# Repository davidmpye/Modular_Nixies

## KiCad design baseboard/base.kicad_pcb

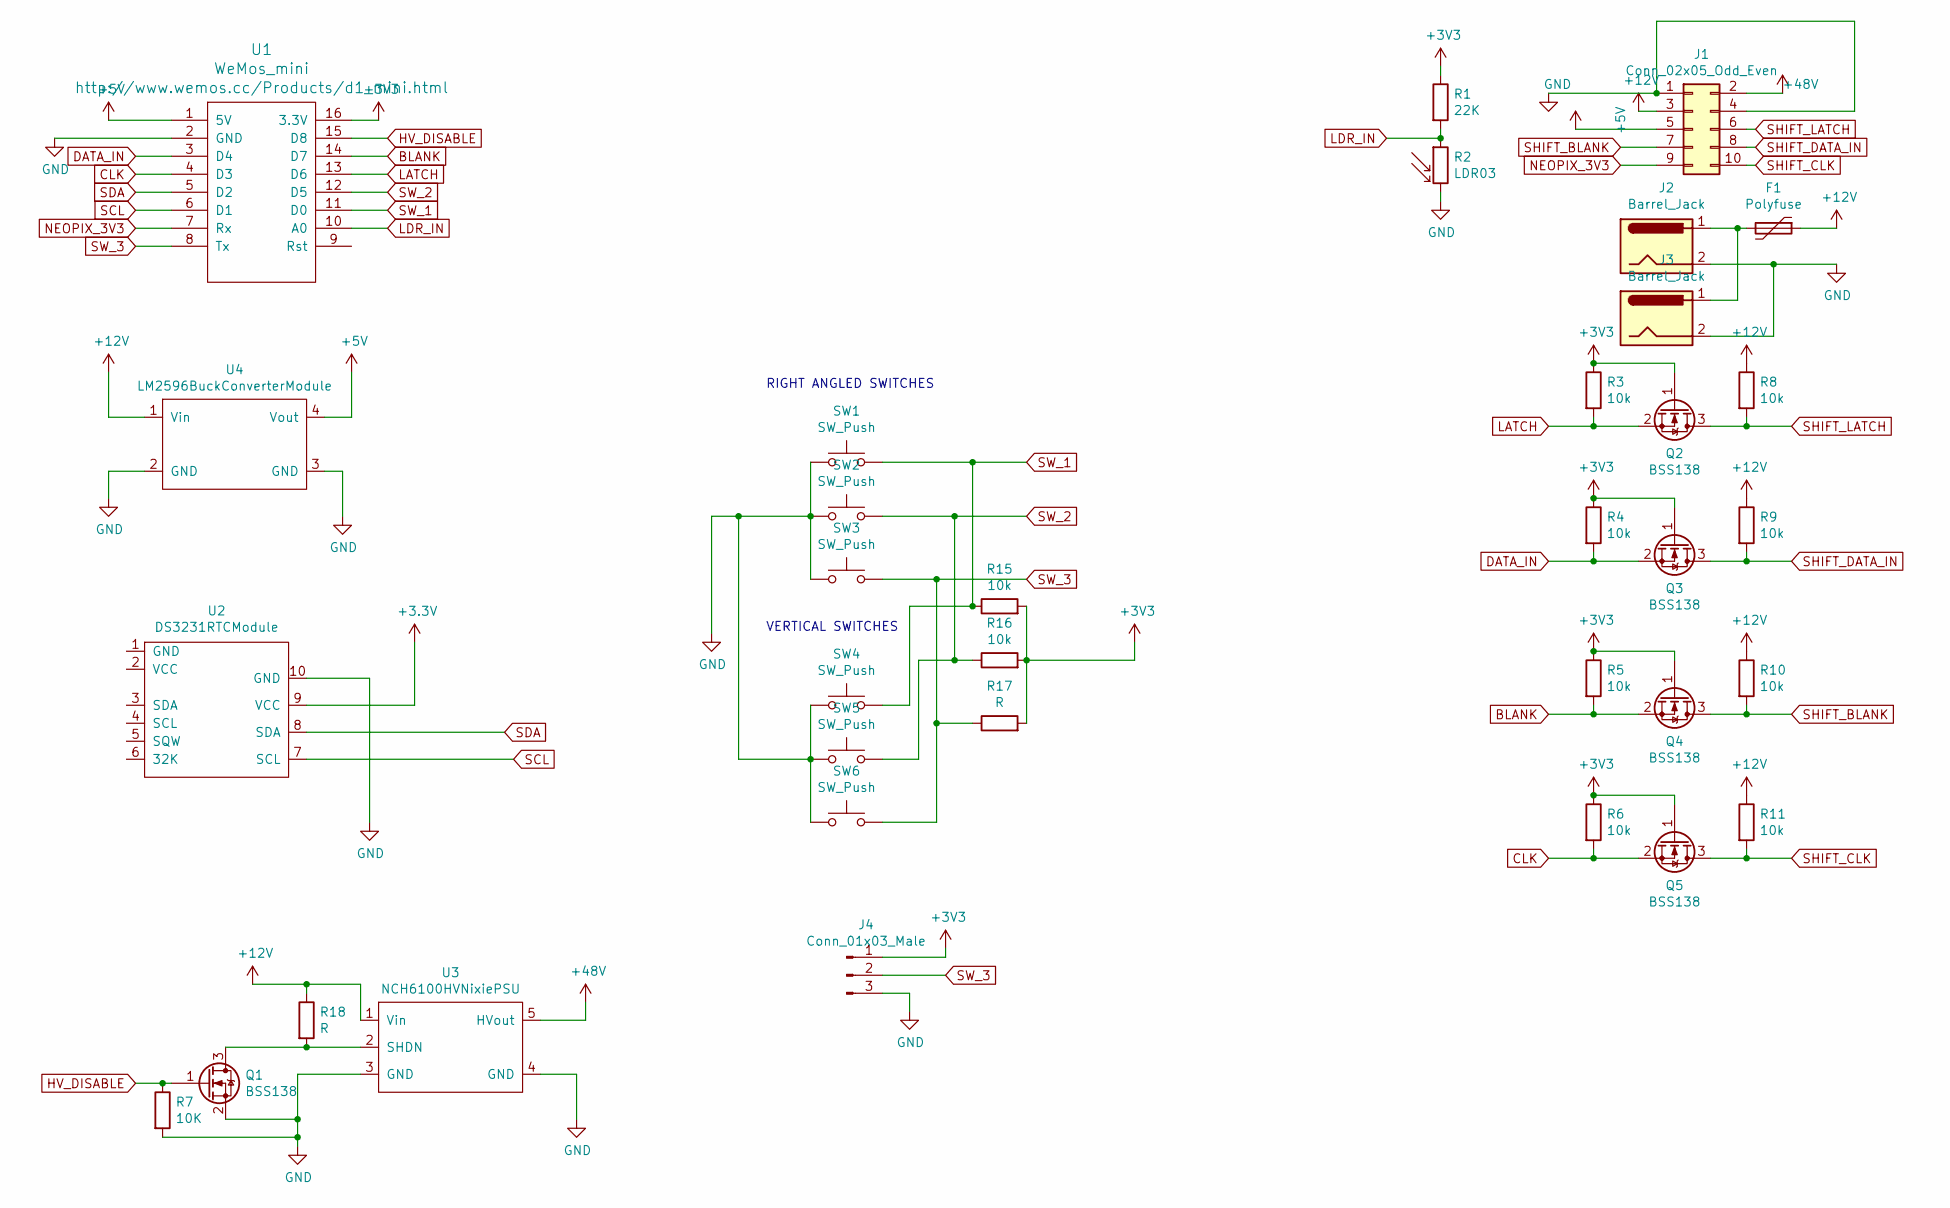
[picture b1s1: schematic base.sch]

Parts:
F1: Polyfuse; R_Axial_DIN0309_L9.0mm_D3.2mm_P15.24mm_Horizontal
J1: Conn_02x05_Odd_Even; PinHeader_2x05_P2.54mm_Vertical
J2: Barrel_Jack; BarrelJack_Horizontal
J3: Barrel_Jack; VerticalBarrel2.1mm
J4: Conn_01x03_Male; PinHeader_1x03_P2.54mm_Vertical
Q1, Q2, Q3, Q4, Q5: BSS138; SOT-23
R1: 22K; R_Axial_DIN0309_L9.0mm_D3.2mm_P12.70mm_Horizontal
R2: LDR03; R_Axial_DIN0204_L3.6mm_D1.6mm_P5.08mm_Vertical
R3, R4, R5, R6, R8, R9, R10, R11: 10k; R_0805_2012Metric_Pad1.15x1.40mm_HandSolder
R7: 10K; R_0805_2012Metric_Pad1.15x1.40mm_HandSolder
R15, R16: 10k; R_Axial_DIN0309_L9.0mm_D3.2mm_P12.70mm_Horizontal
R17, R18: R; R_Axial_DIN0309_L9.0mm_D3.2mm_P12.70mm_Horizontal
SW1, SW2, SW3: SW_Push; SW_Tactile_SKHH_Angled
SW4, SW5, SW6: SW_Push; SW_PUSH_6mm
U1: WeMos_mini; D1_mini_board
U2: DS3231RTCModule; DS3121RTCModule
U3: NCH6100HVNixiePSU
U4: LM2596BuckConverterModule

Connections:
+5V: J1.5, U1.1 (5V), U4.4 (Vout)
+12V: F1.1, J1.3, R8.1, R9.1, R10.1, R11.1, R18.1, U3.1 (Vin), U4.1 (Vin)
+48V: J1.2, U3.5 (HVout)
BLANK: Q4.2 (S), R5.2, U1.14 (D7)
CLK: Q5.2 (S), R6.2, U1.4 (D3)
DATA_IN: Q3.2 (S), R4.2, U1.3 (D4)
GND: J1.1, J1.4, J2.2, J3.2, J4.3, Q1.2 (S), R2.2, R7.2, SW1.1, SW2.1, SW3.1, SW4.1, SW5.1, SW6.1, U1.2 (GND), U2.10 (GND), U3.3 (GND), U3.4 (GND), U4.2 (GND), U4.3 (GND)
HV_DISABLE: Q1.1 (G), R7.1, U1.15 (D8)
LATCH: Q2.2 (S), R3.2, U1.13 (D6)
LDR_IN: R1.2, R2.1, U1.10 (A0)
NEOPIX_3V3: J1.9, U1.7 (Rx)
unnamed: F1.2, J2.1, J3.1
unnamed: Q1.3 (D), R18.2, U3.2 (SHDN)
SCL: U1.6 (D1), U2.7 (SCL)
SDA: U1.5 (D2), U2.8 (SDA)
SHIFT_BLANK: J1.7, Q4.3 (D), R10.2
SHIFT_CLK: J1.10, Q5.3 (D), R11.2
SHIFT_DATA_IN: J1.8, Q3.3 (D), R9.2
SHIFT_LATCH: J1.6, Q2.3 (D), R8.2
SW_1: R15.1, SW1.2, SW4.2, U1.11 (D0)
SW_2: R16.1, SW2.2, SW5.2, U1.12 (D5)
SW_3: J4.2, R17.1, SW3.2, SW6.2, U1.8 (Tx)

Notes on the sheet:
RIGHT ANGLED SWITCHES
VERTICAL SWITCHES

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
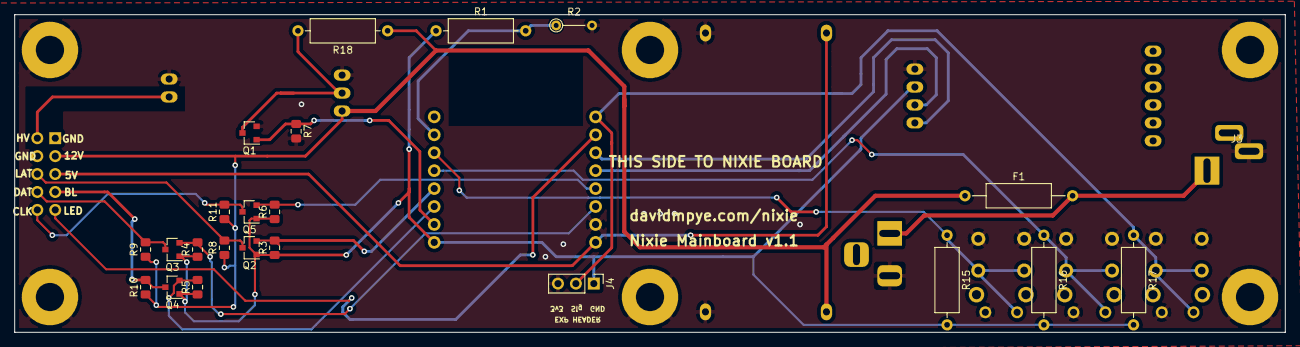
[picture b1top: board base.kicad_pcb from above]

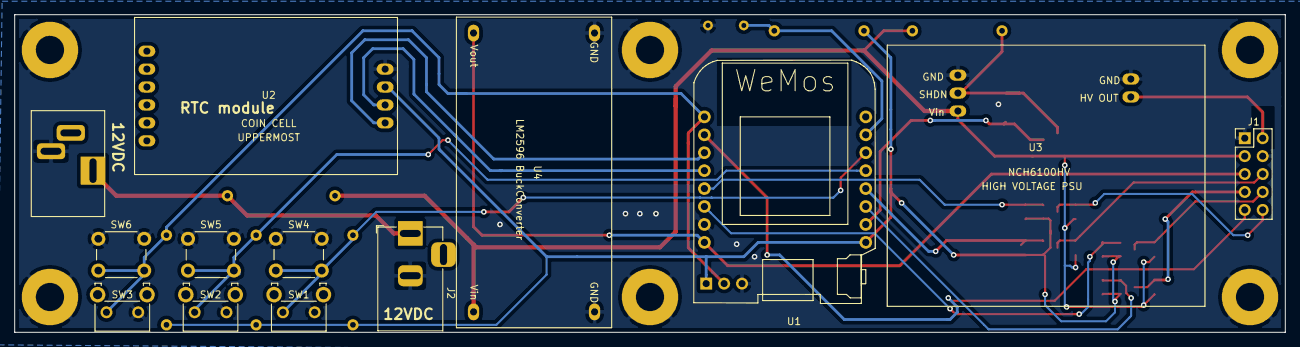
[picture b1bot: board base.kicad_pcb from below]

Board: 2 copper layers, 180.0 x 45.0 mm, 35 parts (12 on the bottom side), 23 nets.

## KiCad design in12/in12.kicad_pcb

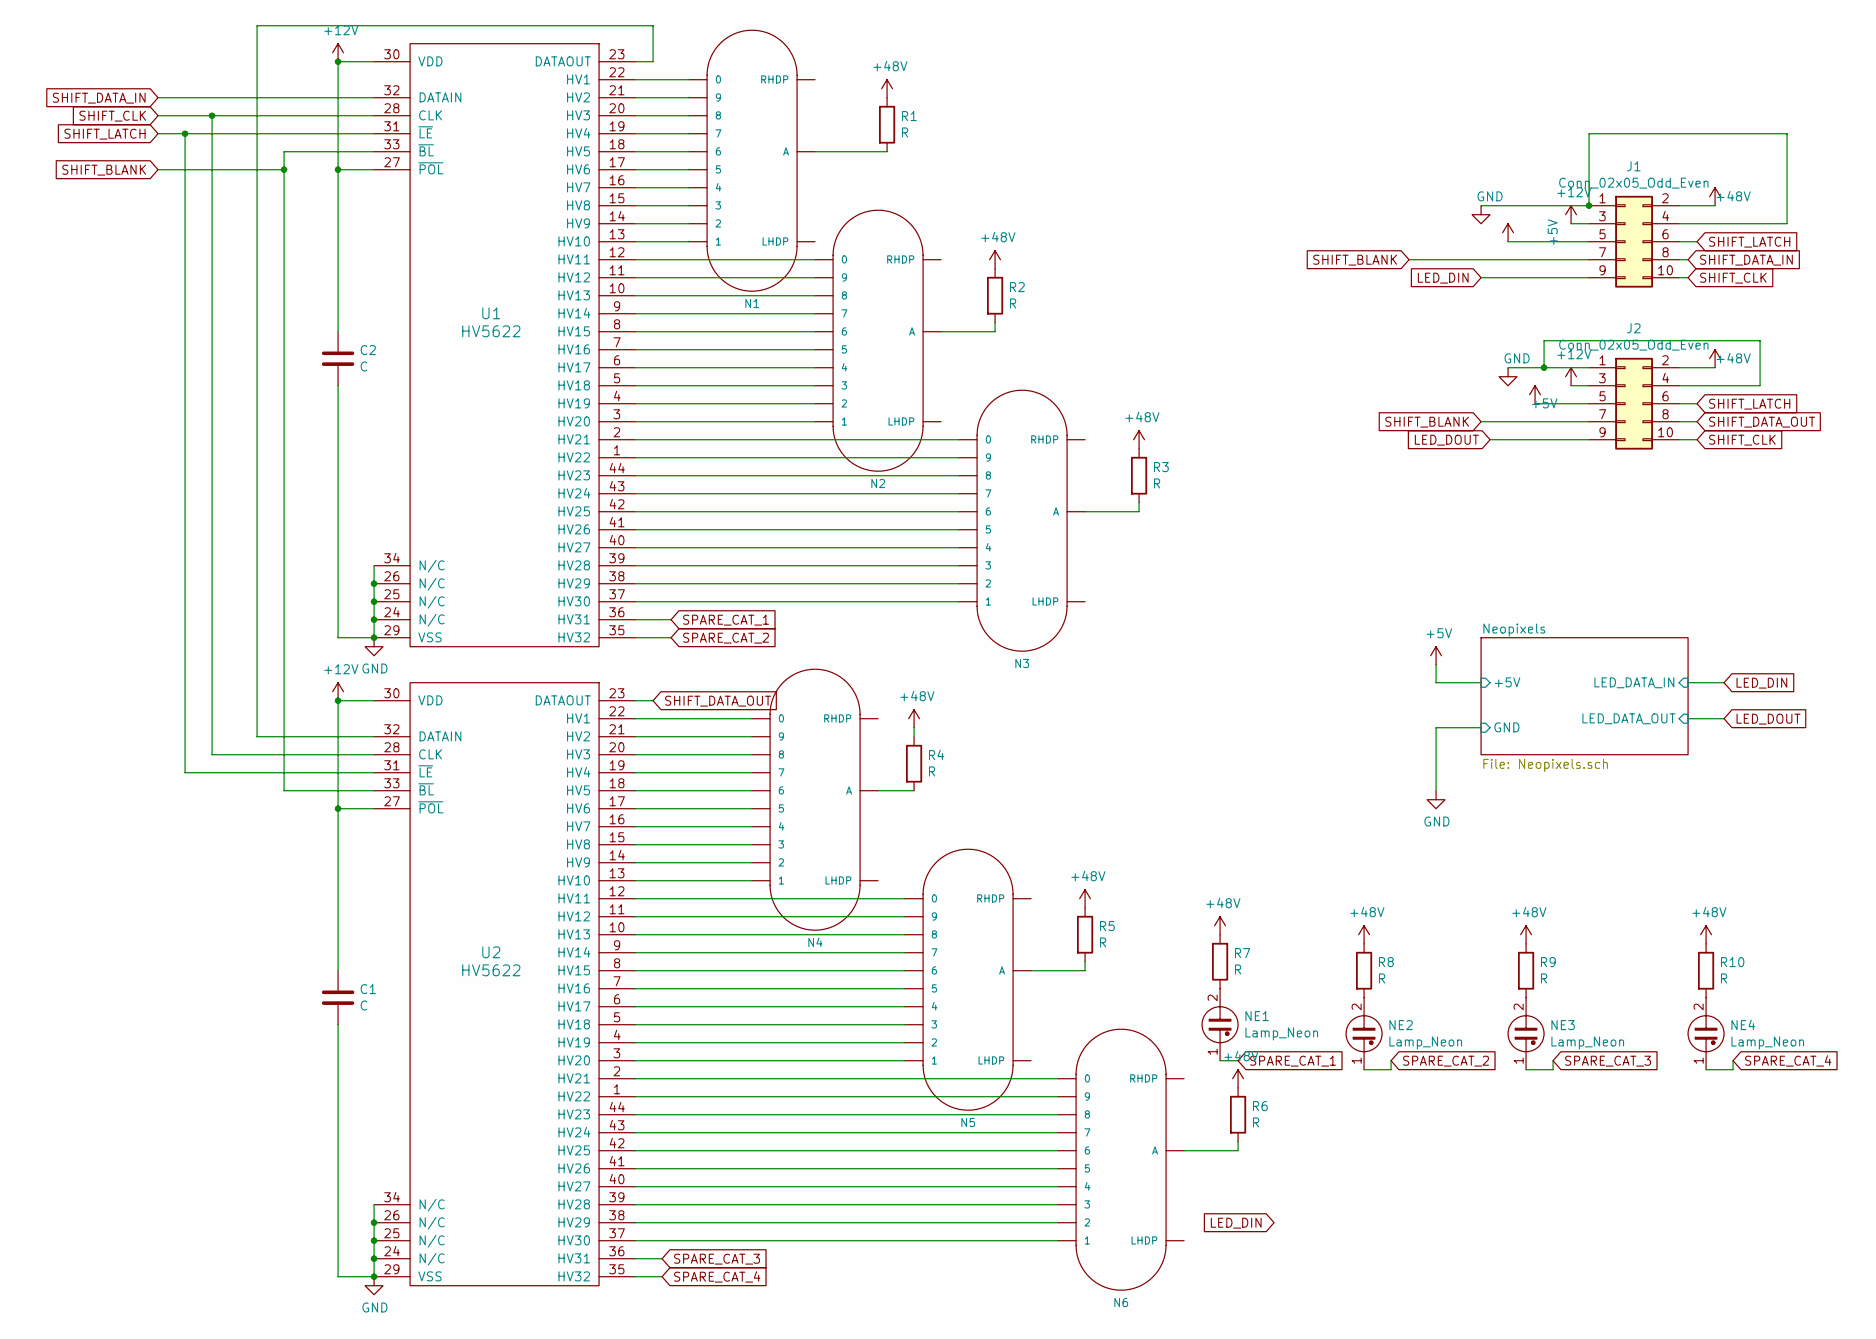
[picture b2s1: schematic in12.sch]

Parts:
C1, C2: C; C_Disc_D4.3mm_W1.9mm_P5.00mm
J1, J2: Conn_02x05_Odd_Even; PinHeader_2x05_P2.54mm_Vertical
N1, N2, N3, N4, N5, N6: IN-14; nixies-us-IN-12-DSUB-NOHOLE
NE1, NE2, NE3, NE4: Lamp_Neon; R_Axial_DIN0207_L6.3mm_D2.5mm_P5.08mm_Vertical
R1, R2, R3, R4, R5, R6, R7, R8, R9, R10: R; R_Axial_DIN0204_L3.6mm_D1.6mm_P7.62mm_Horizontal
U1, U2: HV5622; PQFP-44_10x10mm_P0.8mm

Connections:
+5V: J1.5, J2.5; also elsewhere on the board
+12V: C1.1, C2.1, J1.3, J2.3, U1.27 (~POL), U1.30 (VDD), U2.27 (~POL), U2.30 (VDD)
+48V: J1.2, J2.2, R1.1, R2.1, R3.1, R4.1, R5.1, R6.1, R7.2, R8.1, R9.1, R10.1
GND: C1.2, C2.2, J1.1, J1.4, J2.1, J2.4, U1.24 (N/C), U1.25 (N/C), U1.26 (N/C), U1.29 (VSS), U1.34 (N/C), U2.24 (N/C), U2.25 (N/C), U2.26 (N/C), U2.29 (VSS), U2.34 (N/C); also elsewhere on the board
LED_DIN: J1.9; also elsewhere on the board
LED_DOUT: J2.9; also elsewhere on the board
unnamed: N1.0, U1.22 (HV1)
unnamed: N1.1, U1.13 (HV10)
unnamed: N1.2, U1.14 (HV9)
unnamed: N1.3, U1.15 (HV8)
unnamed: N1.4, U1.16 (HV7)
unnamed: N1.5, U1.17 (HV6)
unnamed: N1.6, U1.18 (HV5)
unnamed: N1.7, U1.19 (HV4)
unnamed: N1.8, U1.20 (HV3)
unnamed: N1.9, U1.21 (HV2)
unnamed: N1.A, R1.2
unnamed: N2.0, U1.12 (HV11)
unnamed: N2.1, U1.3 (HV20)
unnamed: N2.2, U1.4 (HV19)
unnamed: N2.3, U1.5 (HV18)
unnamed: N2.4, U1.6 (HV17)
unnamed: N2.5, U1.7 (HV16)
unnamed: N2.6, U1.8 (HV15)
unnamed: N2.7, U1.9 (HV14)
unnamed: N2.8, U1.10 (HV13)
unnamed: N2.9, U1.11 (HV12)
unnamed: N2.A, R2.2
unnamed: N3.0, U1.2 (HV21)
unnamed: N3.1, U1.37 (HV30)
unnamed: N3.2, U1.38 (HV29)
unnamed: N3.3, U1.39 (HV28)
unnamed: N3.4, U1.40 (HV27)
unnamed: N3.5, U1.41 (HV26)
unnamed: N3.6, U1.42 (HV25)
unnamed: N3.7, U1.43 (HV24)
unnamed: N3.8, U1.44 (HV23)
unnamed: N3.9, U1.1 (HV22)
unnamed: N3.A, R3.2
unnamed: N4.0, U2.22 (HV1)
unnamed: N4.1, U2.13 (HV10)
unnamed: N4.2, U2.14 (HV9)
unnamed: N4.3, U2.15 (HV8)
unnamed: N4.4, U2.16 (HV7)
unnamed: N4.5, U2.17 (HV6)
unnamed: N4.6, U2.18 (HV5)
unnamed: N4.7, U2.19 (HV4)
unnamed: N4.8, U2.20 (HV3)
unnamed: N4.9, U2.21 (HV2)
unnamed: N4.A, R4.2
unnamed: N5.0, U2.12 (HV11)
unnamed: N5.1, U2.3 (HV20)
unnamed: N5.2, U2.4 (HV19)
unnamed: N5.3, U2.5 (HV18)
unnamed: N5.4, U2.6 (HV17)
unnamed: N5.5, U2.7 (HV16)
unnamed: N5.6, U2.8 (HV15)
unnamed: N5.7, U2.9 (HV14)
unnamed: N5.8, U2.10 (HV13)
unnamed: N5.9, U2.11 (HV12)
unnamed: N5.A, R5.2
unnamed: N6.0, U2.2 (HV21)
unnamed: N6.1, U2.37 (HV30)
unnamed: N6.2, U2.38 (HV29)
unnamed: N6.3, U2.39 (HV28)
unnamed: N6.4, U2.40 (HV27)
unnamed: N6.5, U2.41 (HV26)
unnamed: N6.6, U2.42 (HV25)
unnamed: N6.7, U2.43 (HV24)
unnamed: N6.8, U2.44 (HV23)
unnamed: N6.9, U2.1 (HV22)
unnamed: N6.A, R6.2
unnamed: NE1.2, R7.1
unnamed: NE2.2, R8.2
unnamed: NE3.2, R9.2
unnamed: NE4.2, R10.2
unnamed: U1.23 (DATAOUT), U2.32 (DATAIN)
SHIFT_BLANK: J1.7, J2.7, U1.33 (~BL), U2.33 (~BL)
SHIFT_CLK: J1.10, J2.10, U1.28 (CLK), U2.28 (CLK)
SHIFT_DATA_IN: J1.8, U1.32 (DATAIN)
SHIFT_DATA_OUT: J2.8, U2.23 (DATAOUT)
SHIFT_LATCH: J1.6, J2.6, U1.31 (~LE), U2.31 (~LE)
SPARE_CAT_1: NE1.1, U1.36 (HV31)
SPARE_CAT_2: NE2.1, U1.35 (HV32)
SPARE_CAT_3: NE3.1, U2.36 (HV31)
SPARE_CAT_4: NE4.1, U2.35 (HV32)

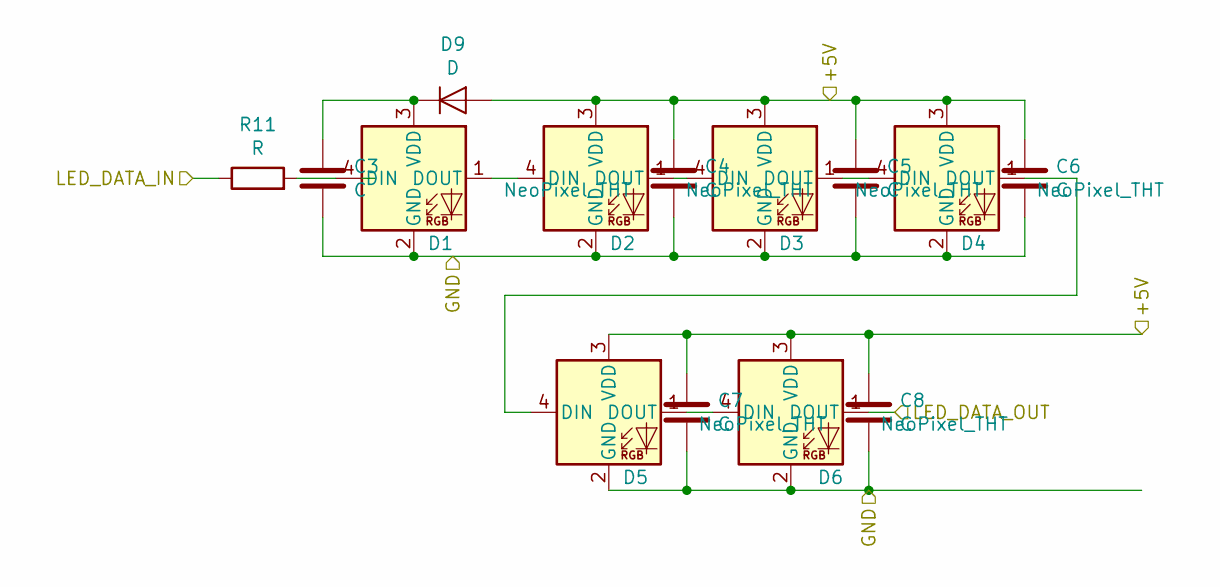
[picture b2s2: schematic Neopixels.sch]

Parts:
C3, C4, C5, C6, C7, C8: C; C_Disc_D4.3mm_W1.9mm_P5.00mm
D1, D2, D3, D4, D5, D6: NeoPixel_THT; LED_D5.0mm-4-Wide
D9: D; D_DO-35_SOD27_P7.62mm_Horizontal
R11: R; R_Axial_DIN0204_L3.6mm_D1.6mm_P7.62mm_Horizontal

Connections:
+5V: C4.1, C5.1, C6.1, C7.1, C8.1, D2.3 (VDD), D3.3 (VDD), D4.3 (VDD), D5.3 (VDD), D6.3 (VDD), D9.2 (A); also elsewhere on the board
GND: C3.2, C4.2, C5.2, C6.2, C7.2, C8.2, D1.2 (GND), D2.2 (GND), D3.2 (GND), D4.2 (GND), D5.2 (GND), D6.2 (GND); also elsewhere on the board
LED_DIN: R11.1; also elsewhere on the board
LED_DOUT: D6.1 (DOUT); also elsewhere on the board
unnamed: C3.1, D1.3 (VDD), D9.1 (K)
unnamed: D1.1 (DOUT), D2.4 (DIN)
unnamed: D1.4 (DIN), R11.2
unnamed: D2.1 (DOUT), D3.4 (DIN)
unnamed: D3.1 (DOUT), D4.4 (DIN)
unnamed: D4.1 (DOUT), D5.4 (DIN)
unnamed: D5.1 (DOUT), D6.4 (DIN)

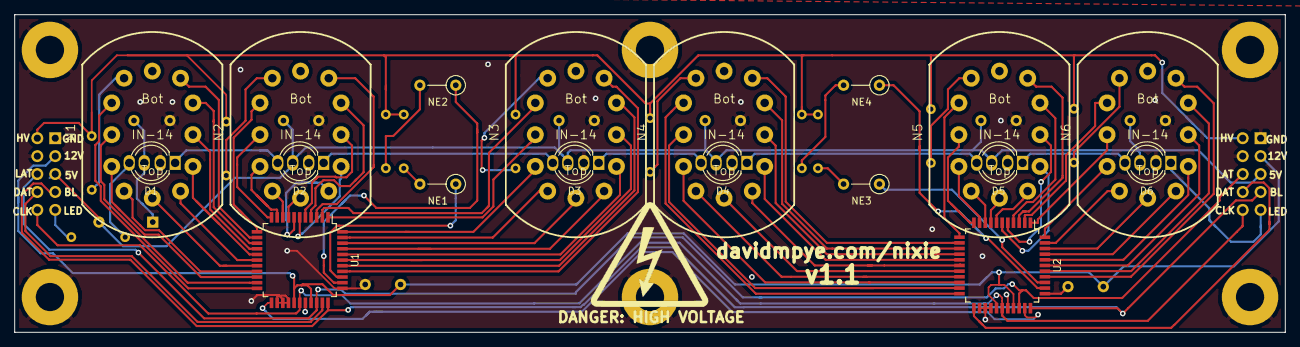
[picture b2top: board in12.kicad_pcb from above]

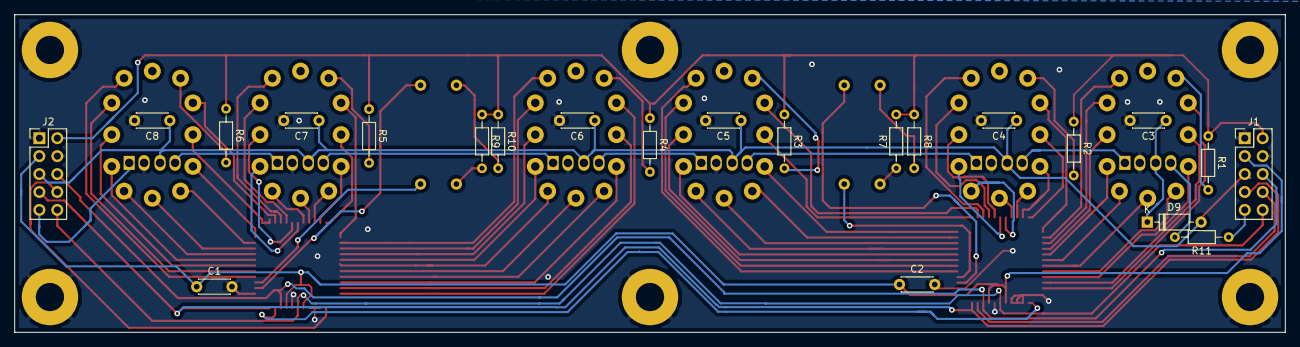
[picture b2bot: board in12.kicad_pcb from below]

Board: 2 copper layers, 180.0 x 45.0 mm, 40 parts (22 on the bottom side), 93 nets.

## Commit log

2019-11-07 Initial import of baseboard design
2019-11-07 Initial import of IN18 topboard
2019-11-07 Initial import of the IN12 topboard
2019-11-09 Fix LED level shifter - should be to +5V, not +12V...
2019-11-19 Remove LED level shifter (using diodes on tube 'boards'), so not needed. Rejig GPIOs as wemos won't boot if D8 is pulled HIGH (and the level shifter *did* pull it high)
2019-12-02 Add pullup resistor to switching FET for HVPSU Remove I2C pullups (they aren't needed, as the RTC module has built in pullups)
2019-12-02 More refactoring of ESP8266 pinout issues to ensure booting functions correctly
2019-12-02 Fix pulldown
2019-12-02 Track rerouting/tidying
